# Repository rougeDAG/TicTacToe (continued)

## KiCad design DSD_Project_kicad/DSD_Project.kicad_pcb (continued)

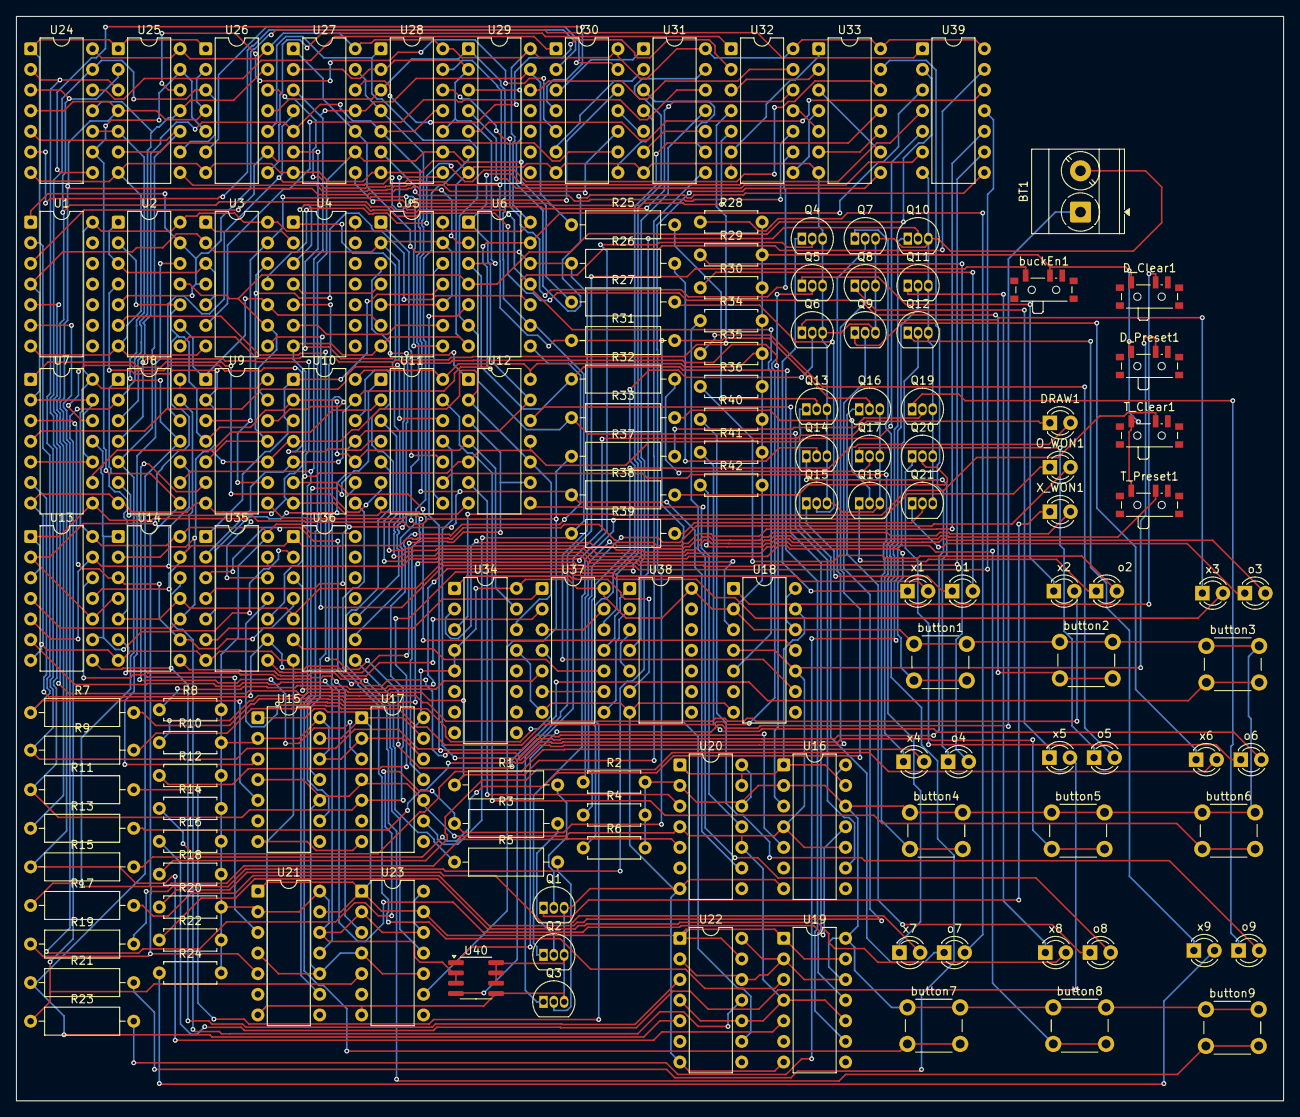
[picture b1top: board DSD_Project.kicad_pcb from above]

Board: 2 copper layers, 156.0 x 133.5 mm, 139 parts (0 on the bottom side), 198 nets.
